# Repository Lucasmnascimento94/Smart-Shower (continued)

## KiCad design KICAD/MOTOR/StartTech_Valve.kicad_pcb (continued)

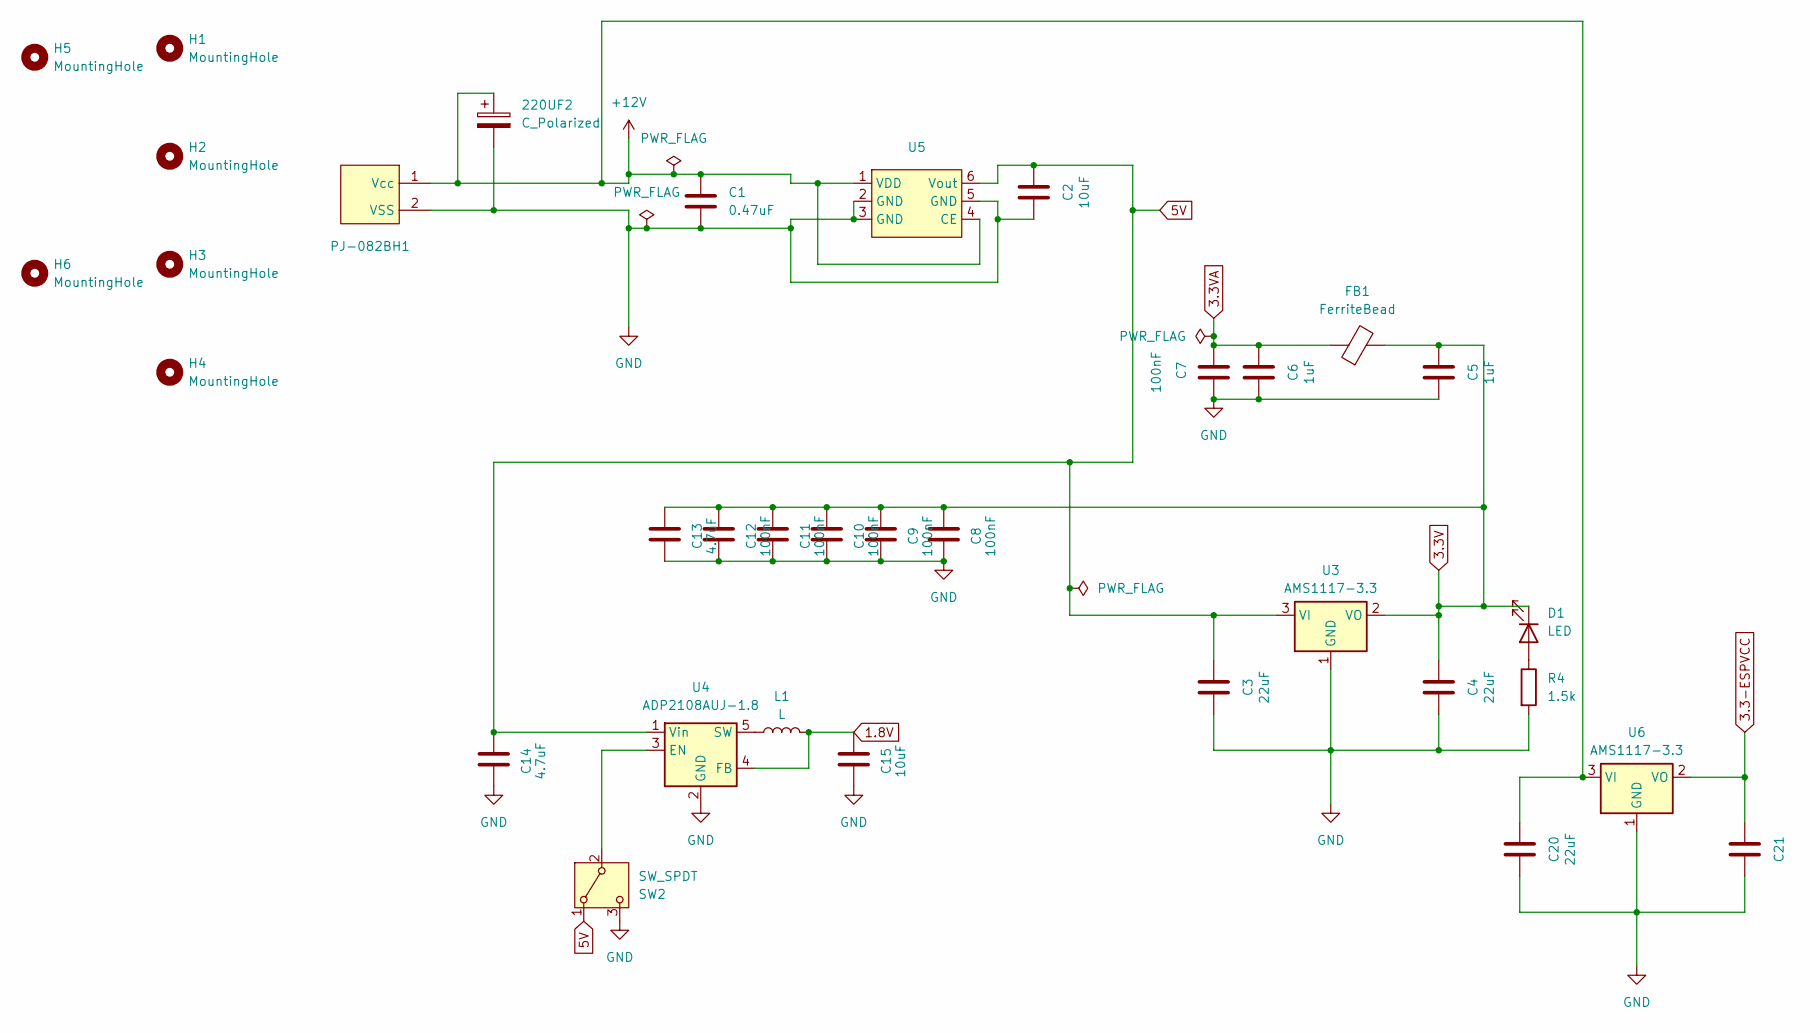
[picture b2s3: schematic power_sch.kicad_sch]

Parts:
220UF2: C_Polarized; C_Disc_D3.0mm_W1.6mm_P2.50mm
C1: 0.47uF; C_0603_1608Metric
C2, C15: 10uF; C_0805_2012Metric
C3, C4, C20, C21: 22uF; C_0805_2012Metric
C5, C6: 1uF; C_0603_1608Metric
C7, C8, C9, C10, C11, C12: 100nF; C_0402_1005Metric
C13, C14: 4.7uF; C_0603_1608Metric
D1: LED; LED_0603_1608Metric
FB1: FerriteBead; L_0603_1608Metric
H1, H2, H3, H4, H5, H6: MountingHole; MountingHole_3.2mm_M3_DIN965
L1: L; L_0603_1608Metric_Pad1.05x0.95mm_HandSolder
PJ-082BH1: BarrelJack_CUI_PJ-063AH_Horizontal
R4: 1.5k; R_0402_1005Metric
SW2: SW_SPDT; SW_Slide_SPDT_Straight_CK_OS102011MS2Q
U3, U6: AMS1117-3.3; SOT-223-3_TabPin2
U4: ADP2108AUJ-1.8; TSOT-23-5
U5: R1501S050B-E2-FE

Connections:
1.8V: C15.1, L1.2, U4.4 (FB); also elsewhere on the board
3.3-ESPVCC: C21.2, U6.2 (VO); also elsewhere on the board
3.3V: C4.2, C5.2, C8.1, C9.1, C10.1, C11.1, C12.1, C13.1, D1.1 (K), FB1.2, U3.2 (VO); also elsewhere on the board
3.3VA: C6.2, C7.2, FB1.1; also elsewhere on the board
5V: C2.2, C3.2, C14.1, SW2.1 (A), U3.3 (VI), U4.1 (Vin), U5.6 (Vout)
+12V: 220UF2.1, C1.1, C20.2, PJ-082BH1.1 (Vcc), U5.1 (VDD), U5.4 (CE), U6.3 (VI); also elsewhere on the board
GND: 220UF2.2, C1.2, C2.1, C3.1, C4.1, C5.1, C6.1, C7.1, C8.2, C9.2, C10.2, C11.2, C12.2, C13.2, C14.2, C15.2, C20.1, C21.1, PJ-082BH1.2 (VSS), R4.2, SW2.3 (C), U3.1 (GND), U4.2 (GND), U5.2 (GND), U5.3 (GND), U5.5 (GND), U6.1 (GND); also elsewhere on the board
unnamed: D1.2 (A), R4.1
unnamed: SW2.2 (B), U4.3 (EN)
unnamed: L1.1, U4.5 (SW)

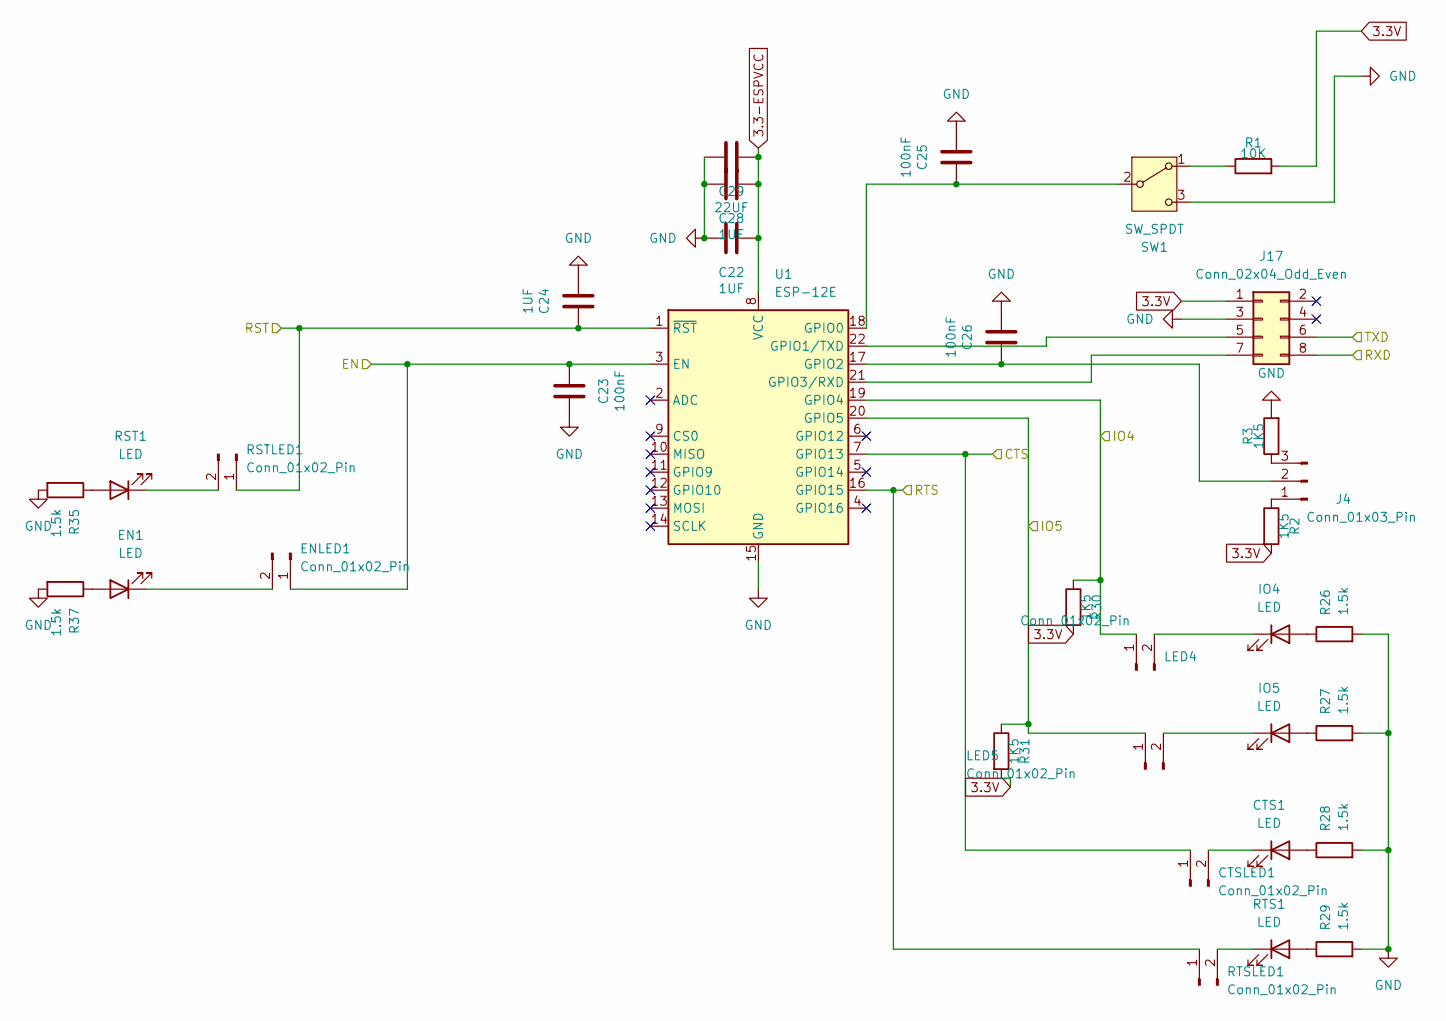
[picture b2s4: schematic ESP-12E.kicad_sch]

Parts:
C22, C24, C28: 1UF; C_0805_2012Metric
C23, C25, C26: 100nF; C_0805_2012Metric
C29: 22UF; C_0805_2012Metric
CTS1: LED; LED_0603_1608Metric
CTSLED1: Conn_01x02_Pin; PinSocket_1x02_P2.54mm_Vertical
EN1: LED; LED_0603_1608Metric
ENLED1: Conn_01x02_Pin; PinSocket_1x02_P2.54mm_Vertical
IO4, IO5: LED; LED_0603_1608Metric
J4: Conn_01x03_Pin; PinSocket_1x03_P2.54mm_Vertical
J17: Conn_02x04_Odd_Even; PinSocket_2x04_P2.54mm_Vertical
LED4, LED5: Conn_01x02_Pin; PinSocket_1x02_P2.54mm_Vertical
R1: 10K; R_0402_1005Metric
R2, R3, R30, R31: 1K5; R_0402_1005Metric
R26, R27, R28, R29, R35, R37: 1.5k; R_0402_1005Metric
RST1: LED; LED_0603_1608Metric
RSTLED1: Conn_01x02_Pin; PinSocket_1x02_P2.54mm_Vertical
RTS1: LED; LED_0603_1608Metric
RTSLED1: Conn_01x02_Pin; PinSocket_1x02_P2.54mm_Vertical
SW1: SW_SPDT; SW_Slide_SPDT_Straight_CK_OS102011MS2Q
U1: ESP-12E

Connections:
3.3-ESPVCC: C22.2, C28.2, C29.2, U1.8 (VCC); also elsewhere on the board
3.3V: J17.1, R1.2, R2.2, R30.2, R31.2; also elsewhere on the board
/ESP-12E/CTS: CTSLED1.1, U1.7 (GPIO13); also elsewhere on the board
/ESP-12E/EN: C23.2, ENLED1.1, U1.3 (EN); also elsewhere on the board
/ESP-12E/IO4: LED4.1, R30.1, U1.19 (GPIO4); also elsewhere on the board
/ESP-12E/IO5: LED5.1, R31.1, U1.20 (GPIO5); also elsewhere on the board
/ESP-12E/RST: C24.2, RSTLED1.1, U1.1 (~RST); also elsewhere on the board
/ESP-12E/RTS: RTSLED1.1, U1.16 (GPIO15); also elsewhere on the board
/ESP-12E/RXD: J17.8; also elsewhere on the board
/ESP-12E/TXD: J17.6; also elsewhere on the board
GND: C22.1, C23.1, C24.1, C25.1, C26.1, C28.1, C29.1, J17.3, R3.2, R26.2, R27.2, R28.2, R29.2, R35.2, R37.2, SW1.3 (C), U1.15 (GND); also elsewhere on the board
unnamed: CTS1.2 (A), R28.1
unnamed: CTS1.1 (K), CTSLED1.2
unnamed: EN1.2 (A), R37.1
unnamed: EN1.1 (K), ENLED1.2
unnamed: IO4.2 (A), R26.1
unnamed: IO4.1 (K), LED4.2
unnamed: IO5.2 (A), R27.1
unnamed: IO5.1 (K), LED5.2
unnamed: J4.1, R2.1
unnamed: C26.2, J4.2, U1.17 (GPIO2)
unnamed: J4.3, R3.1
unnamed: J17.5, U1.22 (GPIO1/TXD)
unnamed: J17.7, U1.21 (GPIO3/RXD)
unnamed: R35.1, RST1.2 (A)
unnamed: RST1.1 (K), RSTLED1.2
unnamed: R29.1, RTS1.2 (A)
unnamed: RTS1.1 (K), RTSLED1.2
unnamed: R1.1, SW1.1 (A)
unnamed: C25.2, SW1.2 (B), U1.18 (GPIO0)

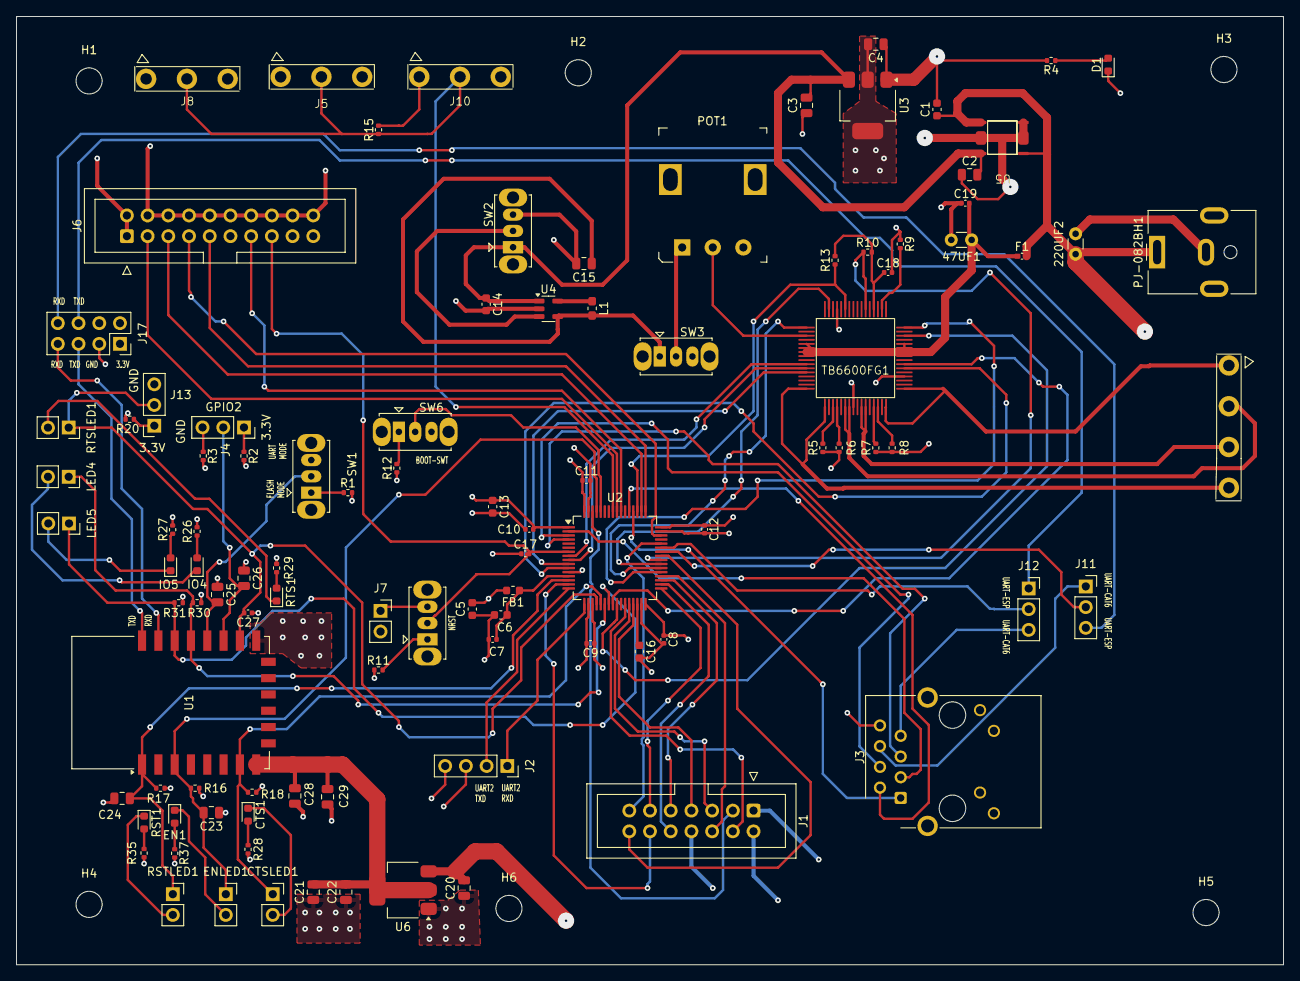
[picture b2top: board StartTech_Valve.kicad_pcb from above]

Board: 4 copper layers, 155.4 x 116.3 mm, 107 parts (0 on the bottom side), 96 nets.

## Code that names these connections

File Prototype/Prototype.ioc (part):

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Mcu.Name=STM32F469IITx
Mcu.Package=LQFP176
Mcu.UserName=STM32F469IITx
PA0/WKUP.Mode=SYS_WakeUp0
PA0/WKUP.Signal=SYS_WKUP
PA1.Mode=RGB888
PA1.Signal=LTDC_R2
PA12.Mode=RGB888
PA12.Signal=LTDC_R5
PA13.Mode=JTAG_5_pins
PA13.Signal=SYS_JTMS-SWDIO
PA14.Mode=JTAG_5_pins
PA14.Signal=SYS_JTCK-SWCLK
PA15.Mode=JTAG_5_pins
PA15.Signal=SYS_JTDI
PA2.Mode=RGB888
PA2.Signal=LTDC_R1
PA3.Mode=RGB888
PA3.Signal=LTDC_B5
PA5.Mode=RGB888
PA5.Signal=LTDC_R4
PA6.Mode=RGB888
PA6.Signal=LTDC_G2
PA7.Mode=Single Bank 1
PA7.Signal=QUADSPI_CLK
PA8.Mode=RGB888
PA8.Signal=LTDC_R6
PA9.GPIOParameters=GPIO_PuPd,GPIO_ModeDefaultEXTI
PA9.GPIO_ModeDefaultEXTI=GPIO_MODE_IT_FALLING
PA9.GPIO_PuPd=GPIO_PULLUP
PA9.Signal=GPXTI9
PB0.Mode=RGB888
PB0.Signal=LTDC_R3
PB1.Signal=ADCx_IN9
PB10.Mode=Single Bank 1
PB10.Signal=QUADSPI_BK1_NCS
PB11.Mode=RGB888
PB11.Signal=LTDC_G5
PB12.Signal=GPIO_Output
PB13.Mode=Full_Duplex_Master
PB13.Signal=SPI2_SCK
PB14.Mode=Full_Duplex_Master
PB14.Signal=SPI2_MISO
PB15.GPIOParameters=GPIO_Label
PB15.GPIO_Label=LCD_T_CS
PB15.Signal=GPIO_Output
PB3.Mode=JTAG_5_pins
PB3.Signal=SYS_JTDO-SWO
PB4.Mode=JTAG_5_pins
PB4.Signal=SYS_JTRST
PB8.Mode=RGB888
PB8.Signal=LTDC_B6
PB9.Mode=RGB888
PB9.Signal=LTDC_B7
PC0.Signal=GPIO_Output
PC1.Signal=GPIO_Output
PC10.Mode=Asynchronous
PC10.Signal=UART4_TX
PC11.Mode=Asynchronous
PC11.Signal=UART4_RX
PC12.Mode=Asynchronous
PC12.Signal=UART5_TX
PC2.Signal=ADCx_IN12
PC3.Mode=Full_Duplex_Master
PC3.Signal=SPI2_MOSI
PC4.GPIOParameters=GPIO_Label
PC4.GPIO_Label=FLASH_RESET
PC4.Signal=GPIO_Output
PC7.Signal=GPIO_Input
PC8.GPIOParameters=GPIO_Label
PC8.GPIO_Label=ESP_RTS
PC8.Signal=GPIO_Output
PD0.Signal=FMC_D2_DA2
PD1.Signal=FMC_D3_DA3
PD10.Signal=FMC_D15_DA15
PD11.Signal=GPIO_Output
PD12.GPIOParameters=GPIO_Label
PD12.GPIO_Label=FMC_LDQM
PD12.Signal=GPIO_Output
PD13.GPIOParameters=GPIO_Label
PD13.GPIO_Label=FMC_UDQM
PD13.Signal=GPIO_Output
PD14.Signal=FMC_D0_DA0
PD15.Signal=FMC_D1_DA1
PD2.Mode=Asynchronous
PD2.Signal=UART5_RX
PD3.Mode=RGB888
PD3.Signal=LTDC_G7
PD4.GPIOParameters=GPIO_Label
PD4.GPIO_Label=ESP_RST
PD4.Signal=GPIO_Output
PD5.GPIOParameters=GPIO_PuPd,GPIO_Label,GPIO_ModeDefaultOutputPP
PD5.GPIO_Label=ESP_EN
PD5.GPIO_ModeDefaultOutputPP=GPIO_MODE_OUTPUT_OD
PD5.GPIO_PuPd=GPIO_PULLUP
PD5.Signal=GPIO_Output
PD6.Mode=RGB888
PD6.Signal=LTDC_B2
PD8.Signal=FMC_D13_DA13
PD9.Signal=FMC_D14_DA14
PE0.Mode=Asynchronous
PE0.Signal=UART8_RX
PE1.Mode=Asynchronous
PE1.Signal=UART8_TX
PE10.Signal=FMC_D7_DA7
PE11.Signal=FMC_D8_DA8
PE12.Signal=FMC_D9_DA9
PE13.Signal=FMC_D10_DA10
PE14.Signal=FMC_D11_DA11
PE15.Signal=FMC_D12_DA12
PE2.Mode=Single Bank 1
PE2.Signal=QUADSPI_BK1_IO2
PE4.Mode=RGB888
PE4.Signal=LTDC_B0
PE5.Mode=RGB888
PE5.Signal=LTDC_G0
PE6.Mode=RGB888
PE6.Signal=LTDC_G1
PE7.Signal=FMC_D4_DA4
PE8.Signal=FMC_D5_DA5
PE9.Signal=FMC_D6_DA6
PF0.Signal=FMC_A0
PF1.Signal=FMC_A1
PF10.Mode=RGB888
PF10.Signal=LTDC_DE
PF11.Signal=FMC_SDNRAS
PF12.Signal=FMC_A6
PF13.Signal=FMC_A7
PF14.Signal=FMC_A8
PF15.Signal=FMC_A9
PF2.Signal=FMC_A2
PF3.Signal=FMC_A3
PF4.Signal=FMC_A4
PF5.Signal=FMC_A5
PF6.Mode=Single Bank 1
PF6.Signal=QUADSPI_BK1_IO3
PF7.Signal=GPIO_Input
PF8.Mode=Single Bank 1
PF8.Signal=QUADSPI_BK1_IO0
PF9.Mode=Single Bank 1
PF9.Signal=QUADSPI_BK1_IO1
PG0.Signal=FMC_A10
PG1.Signal=FMC_A11
PG10.Mode=RGB888
PG10.Signal=LTDC_G3
PG11.Mode=RGB888
PG11.Signal=LTDC_B3
PG12.Mode=RGB888
PG12.Signal=LTDC_B1
PG15.Signal=FMC_SDNCAS
PG2.Signal=FMC_A12
PG4.Signal=FMC_A14_BA0
PG5.Signal=FMC_A15_BA1
PG6.Mode=RGB888
PG6.Signal=LTDC_R7
PG7.Mode=RGB888
PG7.Signal=LTDC_CLK
PG8.Signal=FMC_SDCLK
PH2.Mode=RGB888
PH2.Signal=LTDC_R0
PH4.Mode=RGB888
PH4.Signal=LTDC_G4
PH5.Signal=FMC_SDNWE
PH6.Mode=SdramChipSelect2_1
PH6.Signal=FMC_SDNE1
PH7.Mode=SdramChipSelect2_1
PH7.Signal=FMC_SDCKE1
PI10.Mode=RGB888
PI10.Signal=LTDC_HSYNC
PI11.Mode=RGB888
PI11.Signal=LTDC_G6
PI4.Mode=RGB888
PI4.Signal=LTDC_B4
PI6.Signal=GPIO_Input
PI7.Signal=GPIO_Output
PI9.Mode=RGB888
PI9.Signal=LTDC_VSYNC
RCC.HSE_VALUE=25000000
RCC.SYSCLKFreq_VALUE=180000000
RCC.SYSCLKSource=RCC_SYSCLKSOURCE_PLLCLK
board=custom

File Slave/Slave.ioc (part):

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Mcu.Name=STM32F411R(C-E)Tx
Mcu.Package=LQFP64
Mcu.UserName=STM32F411RCTx
PA0-WKUP.GPIOParameters=GPIO_Label
PA0-WKUP.GPIO_Label=ESP_RST
PA0-WKUP.Signal=GPIO_Output
PA1.Mode=Full_Duplex_Master
PA1.Signal=SPI4_MOSI
PA10.Mode=Asynchronous
PA10.Signal=USART1_RX
PA11.Mode=Full_Duplex_Master
PA11.Signal=SPI4_MISO
PA13.Mode=JTAG_5_pins
PA13.Signal=SYS_JTMS-SWDIO
PA14.Mode=JTAG_5_pins
PA14.Signal=SYS_JTCK-SWCLK
PA15.GPIOParameters=GPIO_Label
PA15.GPIO_Label=LCD_T_DIN
PA15.Mode=JTAG_5_pins
PA15.Signal=SYS_JTDI
PA2.Mode=Asynchronous
PA2.Signal=USART2_TX
PA3.Mode=Asynchronous
PA3.Signal=USART2_RX
PA4.GPIOParameters=GPIO_Label
PA4.GPIO_Label=ESP_RTS
PA4.Signal=GPIO_Output
PA5.GPIOParameters=GPIO_Label
PA5.GPIO_Label=ESP_CTS
PA5.Signal=GPIO_Input
PA6.GPIOParameters=GPIO_Label
PA6.GPIO_Label=ESP_IO4
PA6.Signal=GPIO_Output
PA7.GPIOParameters=GPIO_Label
PA7.GPIO_Label=ESP_IO5
PA7.Signal=GPIO_Output
PA8.GPIOParameters=GPIO_ModeDefaultEXTI
PA8.GPIO_ModeDefaultEXTI=GPIO_MODE_IT_FALLING
PA8.Signal=GPXTI8
PA9.Mode=Asynchronous
PA9.Signal=USART1_TX
PB1.GPIOParameters=GPIO_Label
PB1.GPIO_Label=LCD_RST
PB1.Signal=GPIO_Output
PB10.Mode=Full_Duplex_Master
PB10.Signal=SPI2_SCK
PB12.GPIOParameters=GPIO_Label
PB12.GPIO_Label=T_CS
PB12.Signal=GPIO_Output
PB13.Mode=Full_Duplex_Master
PB13.Signal=SPI4_SCK
PB14.Mode=Full_Duplex_Master
PB14.Signal=SPI2_MISO
PB15.Mode=Full_Duplex_Master
PB15.Signal=SPI2_MOSI
PB2.GPIOParameters=GPIO_Label
PB2.GPIO_Label=LCD_DC
PB2.Signal=GPIO_Output
PB3.Mode=JTAG_5_pins
PB3.Signal=SYS_JTDO-SWO
PB4.Mode=JTAG_5_pins
PB4.Signal=SYS_JTRST
PB5.GPIOParameters=GPIO_Speed,PinState,GPIO_PuPd,GPIO_Label,GPIO_ModeDefaultOutputPP
PB5.GPIO_Label=OneWire
PB5.GPIO_ModeDefaultOutputPP=GPIO_MODE_OUTPUT_OD
PB5.GPIO_PuPd=GPIO_NOPULL
PB5.GPIO_Speed=GPIO_SPEED_FREQ_HIGH
PB5.PinState=GPIO_PIN_SET
PB5.Signal=GPIO_Output
PB7.Signal=GPIO_Output
PB8.GPIOParameters=GPIO_Label
PB8.GPIO_Label=ESP_EN
PB8.Signal=GPIO_Output
PB9.GPIOParameters=GPIO_Label
PB9.GPIO_Label=LCD_CS
PB9.Signal=GPIO_Output
PC0.GPIOParameters=GPIO_Label
PC0.GPIO_Label=Valve_M1
PC0.Signal=GPIO_Output
PC1.GPIOParameters=GPIO_Label
PC1.GPIO_Label=Valve_M2
PC1.Signal=GPIO_Output
PC10.GPIOParameters=GPIO_Label
PC10.GPIO_Label=Valve_ALERT
PC10.Signal=GPXTI10
PC2.GPIOParameters=GPIO_Label
PC2.GPIO_Label=Valve_M3
PC2.Signal=GPIO_Output
PC3.GPIOParameters=GPIO_Label
PC3.GPIO_Label=Valve_EN
PC3.Signal=GPIO_Output
PC4.GPIOParameters=GPIO_Label
PC4.GPIO_Label=Valve_RST
PC4.Signal=GPIO_Output
PC5.GPIOParameters=GPIO_Label
PC5.GPIO_Label=Valve_CLK
PC5.Signal=GPIO_Output
PC6.GPIOParameters=GPIO_Label
PC6.GPIO_Label=Valve_CCW
PC6.Signal=GPIO_Output
PC7.GPIOParameters=GPIO_Label
PC7.GPIO_Label=Valve_LATCH
PC7.Signal=GPIO_Output
PC8.GPIOParameters=GPIO_Label
PC8.GPIO_Label=Valve_TQ
PC8.Signal=GPIO_Output
PH0\ -\ OSC_IN.GPIOParameters=GPIO_Label
PH0\ -\ OSC_IN.GPIO_Label=LCD_CS
PH0\ -\ OSC_IN.Signal=GPIO_Output
RCC.HSE_VALUE=25000000
RCC.SYSCLKFreq_VALUE=80000000
RCC.SYSCLKSource=RCC_SYSCLKSOURCE_PLLCLK
board=custom

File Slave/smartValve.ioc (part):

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Mcu.Name=STM32F411R(C-E)Tx
Mcu.Package=LQFP64
Mcu.UserName=STM32F411RCTx
PA0-WKUP.GPIOParameters=GPIO_Label
PA0-WKUP.GPIO_Label=ESP_RST
PA0-WKUP.Signal=GPIO_Output
PA1.Mode=Full_Duplex_Master
PA1.Signal=SPI4_MOSI
PA10.Mode=Asynchronous
PA10.Signal=USART1_RX
PA11.Mode=Full_Duplex_Master
PA11.Signal=SPI4_MISO
PA13.Mode=JTAG_5_pins
PA13.Signal=SYS_JTMS-SWDIO
PA14.Mode=JTAG_5_pins
PA14.Signal=SYS_JTCK-SWCLK
PA15.GPIOParameters=GPIO_Label
PA15.GPIO_Label=LCD_T_DIN
PA15.Mode=JTAG_5_pins
PA15.Signal=SYS_JTDI
PA2.Mode=Asynchronous
PA2.Signal=USART2_TX
PA3.Mode=Asynchronous
PA3.Signal=USART2_RX
PA6.GPIOParameters=GPIO_PuPd,GPIO_Label,GPIO_ModeDefaultOutputPP
PA6.GPIO_Label=ESP_IO4(RTS)
PA6.GPIO_ModeDefaultOutputPP=GPIO_MODE_OUTPUT_OD
PA6.GPIO_PuPd=GPIO_NOPULL
PA6.Signal=GPIO_Output
PA7.GPIOParameters=GPIO_PuPd,GPIO_Label,GPIO_ModeDefaultOutputPP
PA7.GPIO_Label=ESP_IO5(CTS)
PA7.GPIO_ModeDefaultOutputPP=GPIO_MODE_OUTPUT_OD
PA7.GPIO_PuPd=GPIO_NOPULL
PA7.Signal=GPIO_Output
PA8.GPIOParameters=GPIO_PuPd,GPIO_ModeDefaultEXTI
PA8.GPIO_ModeDefaultEXTI=GPIO_MODE_IT_FALLING
PA8.GPIO_PuPd=GPIO_PULLUP
PA8.Signal=GPXTI8
PA9.Mode=Asynchronous
PA9.Signal=USART1_TX
PB1.GPIOParameters=GPIO_Label
PB1.GPIO_Label=LCD_RST
PB1.Signal=GPIO_Output
PB10.Mode=Full_Duplex_Master
PB10.Signal=SPI2_SCK
PB12.GPIOParameters=GPIO_Label
PB12.GPIO_Label=T_CS
PB12.Signal=GPIO_Output
PB13.Mode=Full_Duplex_Master
PB13.Signal=SPI4_SCK
PB14.Mode=Full_Duplex_Master
PB14.Signal=SPI2_MISO
PB15.Mode=Full_Duplex_Master
PB15.Signal=SPI2_MOSI
PB2.GPIOParameters=GPIO_Label
PB2.GPIO_Label=LCD_DC
PB2.Signal=GPIO_Output
PB3.Mode=JTAG_5_pins
PB3.Signal=SYS_JTDO-SWO
PB4.Mode=JTAG_5_pins
PB4.Signal=SYS_JTRST
PB5.GPIOParameters=GPIO_Speed,PinState,GPIO_PuPd,GPIO_Label,GPIO_ModeDefaultOutputPP
PB5.GPIO_Label=OneWire
PB5.GPIO_ModeDefaultOutputPP=GPIO_MODE_OUTPUT_OD
PB5.GPIO_PuPd=GPIO_NOPULL
PB5.GPIO_Speed=GPIO_SPEED_FREQ_HIGH
PB5.PinState=GPIO_PIN_SET
PB5.Signal=GPIO_Output
PB7.Signal=GPIO_Output
PB8.GPIOParameters=GPIO_Label
PB8.GPIO_Label=ESP_EN
PB8.Signal=GPIO_Output
PB9.GPIOParameters=GPIO_Label
PB9.GPIO_Label=LCD_CS
PB9.Signal=GPIO_Output
PC0.GPIOParameters=GPIO_Label
PC0.GPIO_Label=Valve_M1
PC0.Signal=GPIO_Output
PC1.GPIOParameters=GPIO_Label
PC1.GPIO_Label=Valve_M2
PC1.Signal=GPIO_Output
PC10.GPIOParameters=GPIO_Label
PC10.GPIO_Label=Valve_ALERT
PC10.Signal=GPXTI10
PC2.GPIOParameters=GPIO_Label
PC2.GPIO_Label=Valve_M3
PC2.Signal=GPIO_Output
PC3.GPIOParameters=GPIO_Label
PC3.GPIO_Label=Valve_EN
PC3.Signal=GPIO_Output
PC4.GPIOParameters=GPIO_Label
PC4.GPIO_Label=Valve_RST
PC4.Signal=GPIO_Output
PC5.GPIOParameters=GPIO_Label
PC5.GPIO_Label=Valve_CLK
PC5.Signal=GPIO_Output
PC6.GPIOParameters=GPIO_Label
PC6.GPIO_Label=Valve_CCW
PC6.Signal=GPIO_Output
PC7.GPIOParameters=GPIO_Label
PC7.GPIO_Label=Valve_LATCH
PC7.Signal=GPIO_Output
PC8.GPIOParameters=GPIO_Label
PC8.GPIO_Label=Valve_TQ
PC8.Signal=GPIO_Output
PH0\ -\ OSC_IN.GPIOParameters=GPIO_Label
PH0\ -\ OSC_IN.GPIO_Label=LCD_CS
PH0\ -\ OSC_IN.Signal=GPIO_Output
RCC.HSE_VALUE=25000000
RCC.SYSCLKFreq_VALUE=80000000
RCC.SYSCLKSource=RCC_SYSCLKSOURCE_PLLCLK
board=custom

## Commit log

2025-05-29 cloning
2025-06-02 Create kicadfiles
2025-06-02 Create ScreenFiles
2025-06-02 Create motorFiles
2025-06-14 valve_version1.3
    Added threads to eliminate issue with lagging while using the motor
2025-06-19 OpenDrain
2025-07-12 Mutex-DMA
    Got Mutex working.
    Got UART_DMA working
2025-07-14 Threads
    - Distributed tasks between threads.
    - Created a function/Thread dedicated for print statements, which solved random crashes
    - Started to move the LCD functions from static to dynamic form, using Memory Pool, to avoid using malloc with RTOS.
2025-07-14 version 1.5
2025-07-17 GUI update
